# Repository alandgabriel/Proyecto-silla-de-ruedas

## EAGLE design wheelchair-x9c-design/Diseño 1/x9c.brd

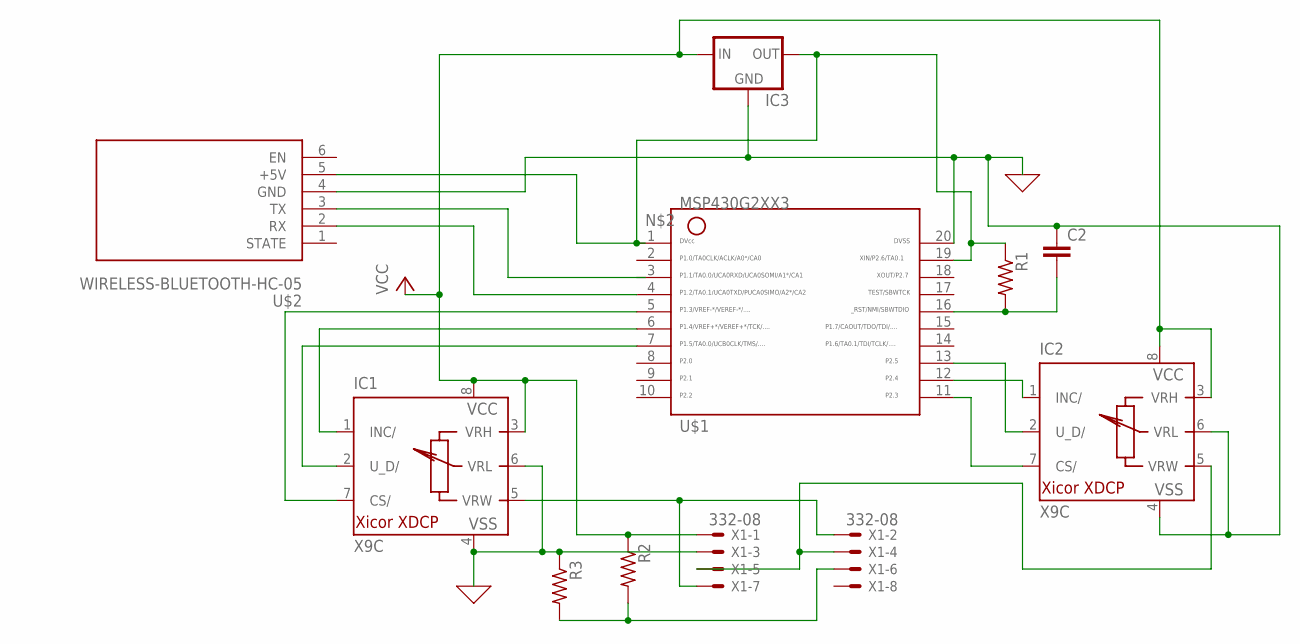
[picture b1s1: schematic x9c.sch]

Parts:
C2: C2,5-3; C2.5-3
IC1, IC2: X9C; DIL08
IC3: 78MXXL
R1, R2, R3: R-US_0204/5; 0204/5
U$1: G2XX3---N20; N20
U$2: WIRELESS-BLUETOOTH-HC-05
X1: 332-08

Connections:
0: C2.1, IC1.4 (VSS), IC1.6 (VRL), IC2.4 (VSS), IC2.6 (VRL), IC3.GND, R3.1, U$1.20, U$2.4 (GND), X1.3
unnamed: U$1.4, U$2.2 (RX)
unnamed: IC3.OUT, R1.1, U$1.1, U$1.19, U$2.5 (+5V)
unnamed: U$1.3, U$2.3 (TX)
unnamed: IC1.7 (CS/), U$1.5
unnamed: IC1.1 (INC/), U$1.6
unnamed: IC1.2 (U_D/), U$1.7
unnamed: C2.2, R1.2, U$1.16
unnamed: IC2.7 (CS/), U$1.11
unnamed: IC2.1 (INC/), U$1.12
unnamed: IC2.2 (U_D/), U$1.13
unnamed: IC1.5 (VRW), X1.2, X1.7
unnamed: IC2.5 (VRW), X1.4, X1.5
unnamed: R2.2, R3.2, X1.6
VCC: IC1.3 (VRH), IC1.8 (VCC), IC2.3 (VRH), IC2.8 (VCC), IC3.IN, R2.1, X1.1

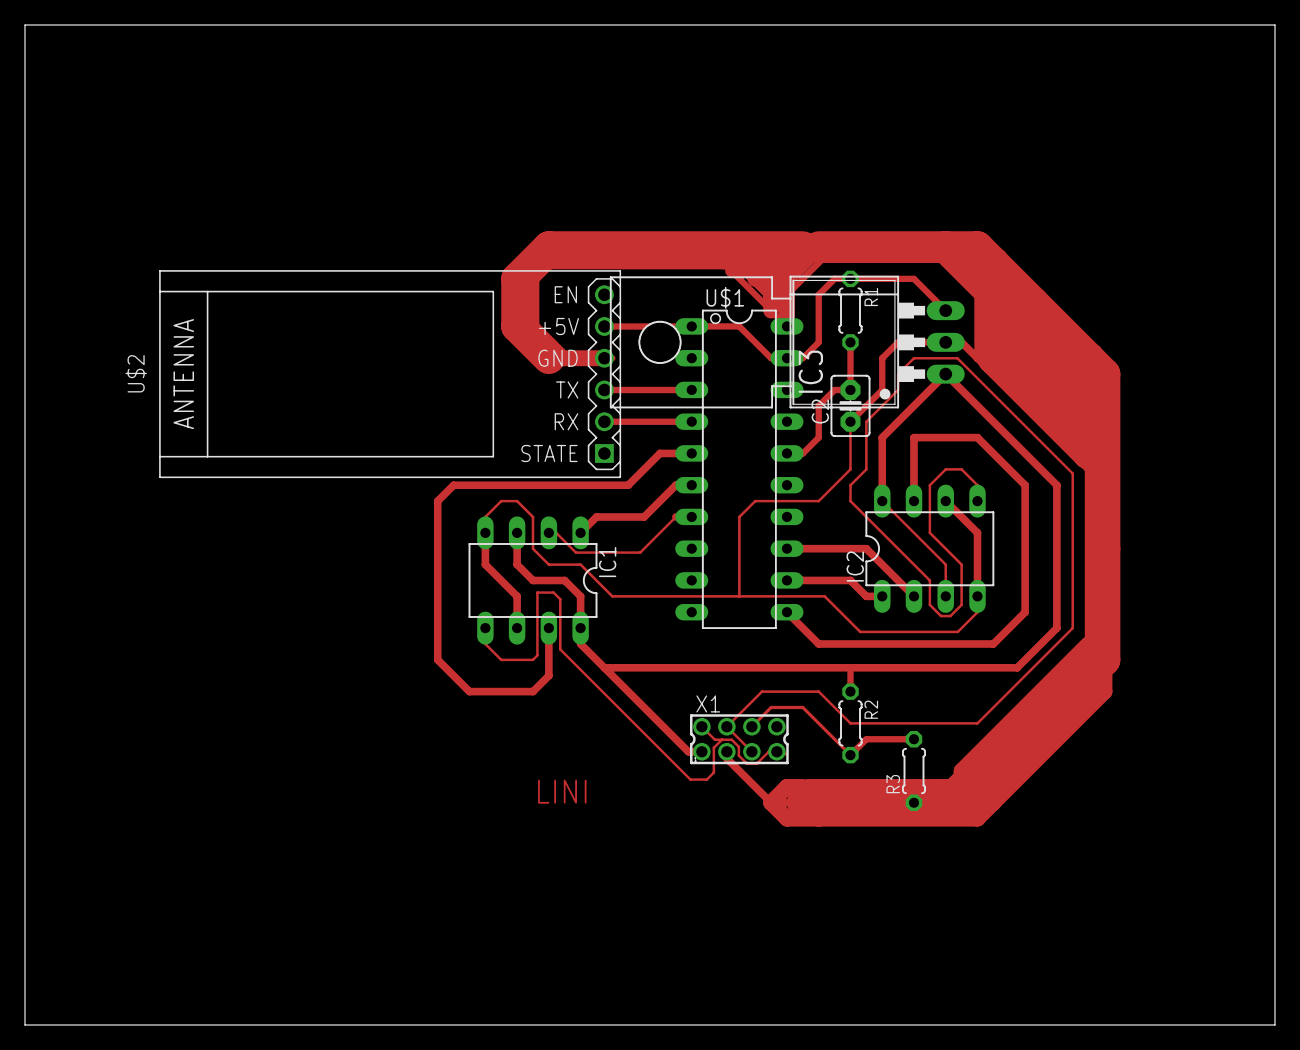
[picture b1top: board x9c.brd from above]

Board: 2 copper layers, 100.0 x 80.0 mm, 10 parts (0 on the bottom side), 15 nets.

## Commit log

2020-01-09 blinking
2020-01-09 adding makefile
2020-01-13 i2c terminado
2020-01-14 i2c y uart implement
2020-09-15 X9C103 control and UART comm
2020-09-27 version final wlchrctrl
2020-10-22 Agregue el diseno PCB y esquematico
2020-11-06 se creo el segundo diseño de pcb

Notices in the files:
parts and their libraries:
diy-modules: Released under the Creative Commons Attribution 4.0 International License: http://creativecommons.org/licenses/by/4.0
